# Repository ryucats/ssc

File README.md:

# Simple Serial Card

## Overview

The Simple Serial Card is a low-cost Super Serial Card work-a-like. I designed
this because I needed a way to use ADTPro on my Apple IIe, and the price of
super serial cards on eBay is getting a bit high for my taste.

This card is more or less 100% compatible with the original Apple card. It
uses the same 6551 ACIA mapped to the same I/O locations, and in fact can
use the same firmware ROM.  It does however have some minor differences in the
interest of cost:

1. There are no DIP switches, so you cannot set the default configuration. It
   does, however, include a jumper that can be removed to disable IRQs.
2. Instead of a DB-25 it is wired to use a DB-9 cable like those used by PC
   motherboards.
3. There is no terminal/modem block to change the serial port wiring. Just use
   the appropriate cable instead, or a null modem adapter.

The KiCAD schematics and PCB layout are included. It is a four layer board,
because my fab house of choice charges the same for 2 and 4 layers, so I went
with what made the layout easier.

## Parts List

* A 74LS245 octal bus transceiver (non-TTL appears to have issues with the ROM address decode logic) (U1)
* A 28-pin 27xx-series EPROM (JEDEC-compatible EEPROMs will also work) (U2)
* A 1.8432 MHz 5V oscillator (U3)
* A 22V10 GAL (any speed or variety should work) (U4)
* A W65C51N ACIA (U5)
* Two MAX232 RS-232 line transceivers (U6, U7)
* Seven 0.1uf ceramic bypass caps (C1-C7)
* Eight 1uf 16V electrolytic caps (C9-C16)
* A 2x5 pin header (J1)
* A 1x2 pin header (J2)

## Assembly

Before assembly you will need to burn firmware ROM into the EEPROM, and burn
the appropriat equations into the GAL. See "Burning the ROM" and "Burning the
GAL" below for more details.

I would suggest socketing all of the chips, but at the very least socket the
ROM and the GAL in case you need to update them.

As mentioned above the header on this card is wired the same as a PC COM
header. There are two varieties of these cables available; this card uses the
newer style which is wired 1:1; that is, pin 1 on the header goes to pin 1
on the DB-9, pin 2 to pin 2, etc. These are sometimes referred to as
"AT/EVEREX" style cables.

There is an asterisk on the card's silkscreen indicating pin one on the RS-232
header; make sure this lines up with pin one on your ribbon cable. Usually this
is the red wire on the ribbon cable.

## Installation

Turn off the computer, put the card in an empty slot, and mount the DB-9 on one
of the small cutouts on the back of the computer (or just run the ribbon cable
through an open cutout if you don't care).

## Design Considerations

Many parts choices were influenced by what I have already in my parts bin, even
if that makes the design non-optimal. For example, I used MAX3232 line drivers
because I have a ton of them. With 12V available on the slots I could've used
different parts and avoided all the charge pump caps, but I didn't feel like
buying more chips.

With the exception of the 22V10 GAL used for glue logic all parts in this design
are still actively available. The GALs are out of production but still readily
available on eBay or Aliexpress (though YMMV as far as quality).

## Burning the ROM

A standard super serial card image should work fine with this card, though
since there are no configuration switches the default settings after power on
or reset will be somewhat random.  Once I have working cards built I will be
creating a customized firmware ROM that sets the defaults to 9600 bps for the
ADT Pro bootstrap.

Since 2K EPROMs are nearly impossible to find I subbed in an AT28C256 EEPROM
(again, I had one already). Only the lower 2K is used by the card, so when
burning you can either duplicate the image 16 times, or fill the upper 30K
with zeroes or some other random data. In theory a AT28C64 EEPROM should also
work (and only waste 6K), but I don't have one to test, and a brief search
suggests they aren't any cheaper than the AT28C256 (presumably because they
are out of production).

I use the TL866 II+ USB programmer along with the minipro Linux client for my
ROM burns.

## Burning the GAL

The equations for the GAL are included as a .pld file for the GALasm program.
If you run Linux or another OS that can run GNU make then you should be able
to just type "make" in the "gal" subfolder to compile the equations into a
.jed file.  Burning this file requires a suitable programmer; I personally
use the same TL866 II+ that I use for burning ROMs, though at least at the time
of this writing the minipro client doesn't know how to burn GALs properly, so
you'll need to use the official client software, either on a Windows PC or
under Wine.

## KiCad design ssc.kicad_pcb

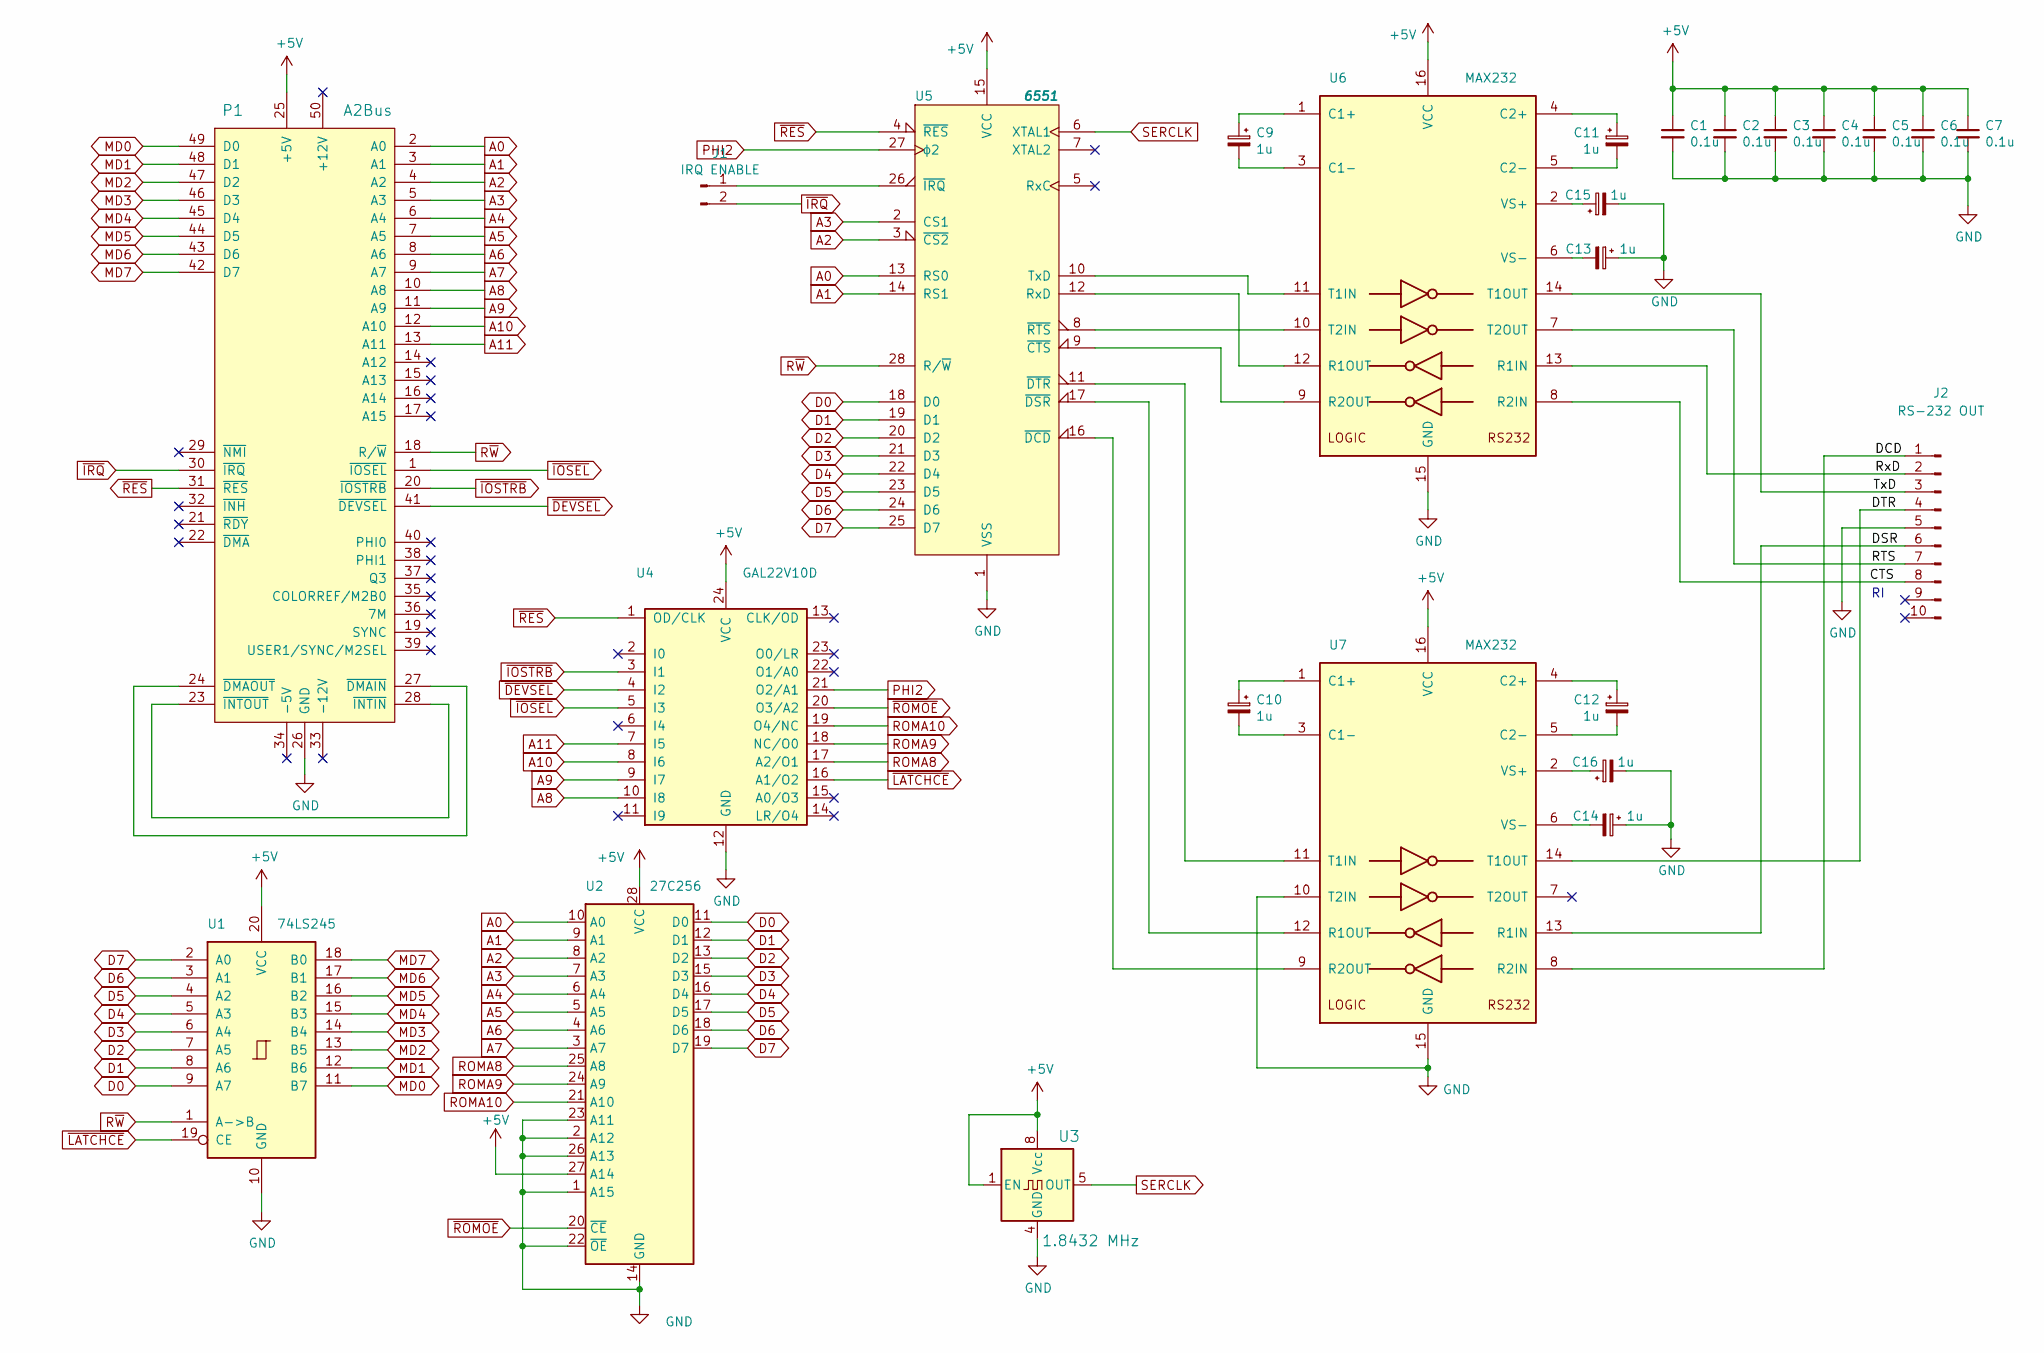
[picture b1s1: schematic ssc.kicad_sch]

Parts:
C1, C2, C3, C4, C5, C6, C7: 0.1u; C_Disc_D4.3mm_W1.9mm_P5.00mm
C9, C10, C11, C12, C13, C14, C15, C16: 1u; CP_Radial_D5.0mm_P2.50mm
J1: IRQ ENABLE; PinHeader_1x02_P2.54mm_Vertical
J2: RS-232 OUT; PinHeader_2x05_P2.54mm_Vertical
P1: A2Bus; Male_Card-Edge_50_pin__100_mil
U1: 74LS245; DIP-20_W7.62mm_Socket
U2: 27C256; DIP-28_W15.24mm
U3: 1.8432 MHz; Oscillator_DIP-8
U4: GAL22V10D; DIP-24_W7.62mm
U5: 6551; DIP-28_W15.24mm
U6, U7: MAX232; DIP-16_W7.62mm_Socket

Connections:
+5V: C1.1, C2.1, C3.1, C4.1, C5.1, C6.1, C7.1, P1.25 (+5V), U1.20 (VCC), U2.27 (A14), U2.28 (VCC), U4.24 (VCC), U5.15 (VCC), U6.16 (VCC), U7.16 (VCC); also elsewhere on the board
/CTS: J2.8, U6.8 (R2IN)
/DCD: J2.1, U7.8 (R2IN)
/DSR: J2.6, U7.13 (R1IN)
/DTR: J2.4, U7.14 (T1OUT)
/RTS: J2.7, U6.7 (T2OUT)
/RxD: J2.2, U6.13 (R1IN)
/TxD: J2.3, U6.14 (T1OUT)
A0: P1.2 (A0), U2.10 (A0), U5.13 (RS0)
A1: P1.3 (A1), U2.9 (A1), U5.14 (RS1)
A2: P1.4 (A2), U2.8 (A2), U5.3 (~CS2)
A3: P1.5 (A3), U2.7 (A3), U5.2 (CS1)
A4: P1.6 (A4), U2.6 (A4)
A5: P1.7 (A5), U2.5 (A5)
A6: P1.8 (A6), U2.4 (A6)
A7: P1.9 (A7), U2.3 (A7)
A8: P1.10 (A8), U4.10 (I8)
A9: P1.11 (A9), U4.9 (I7)
A10: P1.12 (A10), U4.8 (I6)
A11: P1.13 (A11), U4.7 (I5)
D0: U1.9 (A7), U2.11 (D0), U5.18 (D0)
D1: U1.8 (A6), U2.12 (D1), U5.19 (D1)
D2: U1.7 (A5), U2.13 (D2), U5.20 (D2)
D3: U1.6 (A4), U2.15 (D3), U5.21 (D3)
D4: U1.5 (A3), U2.16 (D4), U5.22 (D4)
D5: U1.4 (A2), U2.17 (D5), U5.23 (D5)
D6: U1.3 (A1), U2.18 (D6), U5.24 (D6)
D7: U1.2 (A0), U2.19 (D7), U5.25 (D7)
GND: C1.2, C2.2, C3.2, C4.2, C5.2, C6.2, C7.2, C13.1, C14.1, C15.2, C16.2, J2.5, P1.26 (GND), U1.10 (GND), U2.1 (A15), U2.2 (A12), U2.14 (GND), U2.22 (~OE), U2.23 (A11), U2.26 (A13), U4.12 (GND), U5.1 (VSS), U6.15 (GND), U7.10 (T2IN), U7.15 (GND); also elsewhere on the board
MD0: P1.49 (D0), U1.11 (B7)
MD1: P1.48 (D1), U1.12 (B6)
MD2: P1.47 (D2), U1.13 (B5)
MD3: P1.46 (D3), U1.14 (B4)
MD4: P1.45 (D4), U1.15 (B3)
MD5: P1.44 (D5), U1.16 (B2)
MD6: P1.43 (D6), U1.17 (B1)
MD7: P1.42 (D7), U1.18 (B0)
unnamed: J1.1, U5.26 (~IRQ)
unnamed: P1.24 (~DMAOUT), P1.27 (~DMAIN)
unnamed: P1.23 (~INTOUT), P1.28 (~INTIN)
unnamed: U5.12 (RxD), U6.12 (R1OUT)
unnamed: U5.10 (TxD), U6.11 (T1IN)
unnamed: U5.9 (~CTS), U6.9 (R2OUT)
unnamed: U5.16 (~DCD), U7.9 (R2OUT)
unnamed: U5.17 (~DSR), U7.12 (R1OUT)
unnamed: U5.11 (~DTR), U7.11 (T1IN)
unnamed: U5.8 (~RTS), U6.10 (T2IN)
unnamed: C9.1, U6.1 (C1+)
unnamed: C9.2, U6.3 (C1-)
unnamed: C11.1, U6.4 (C2+)
unnamed: C11.2, U6.5 (C2-)
unnamed: C15.1, U6.2 (VS+)
unnamed: C13.2, U6.6 (VS-)
unnamed: C10.1, U7.1 (C1+)
unnamed: C10.2, U7.3 (C1-)
unnamed: C12.1, U7.4 (C2+)
unnamed: C12.2, U7.5 (C2-)
unnamed: C16.1, U7.2 (VS+)
unnamed: C14.2, U7.6 (VS-)
PHI2: U4.21 (O2/A1), U5.27 (ϕ2)
ROMA8: U2.25 (A8), U4.17 (A2/O1)
ROMA9: U2.24 (A9), U4.18 (NC/O0)
ROMA10: U2.21 (A10), U4.19 (O4/NC)
R~W: P1.18 (R/~W), U1.1 (A->B), U5.28 (R/~W)
SERCLK: U5.6 (XTAL1); also elsewhere on the board
~DEVSEL: P1.41 (~DEVSEL), U4.4 (I2)
~IOSEL: P1.1 (~IOSEL), U4.5 (I3)
~IOSTRB: P1.20 (~IOSTRB), U4.3 (I1)
~IRQ: J1.2, P1.30 (~IRQ)
~LATCHCE: U1.19 (CE), U4.16 (A1/O2)
~RES: P1.31 (~RES), U4.1 (OD/CLK), U5.4 (~RES)
~ROMOE: U2.20 (~CE), U4.20 (O3/A2)

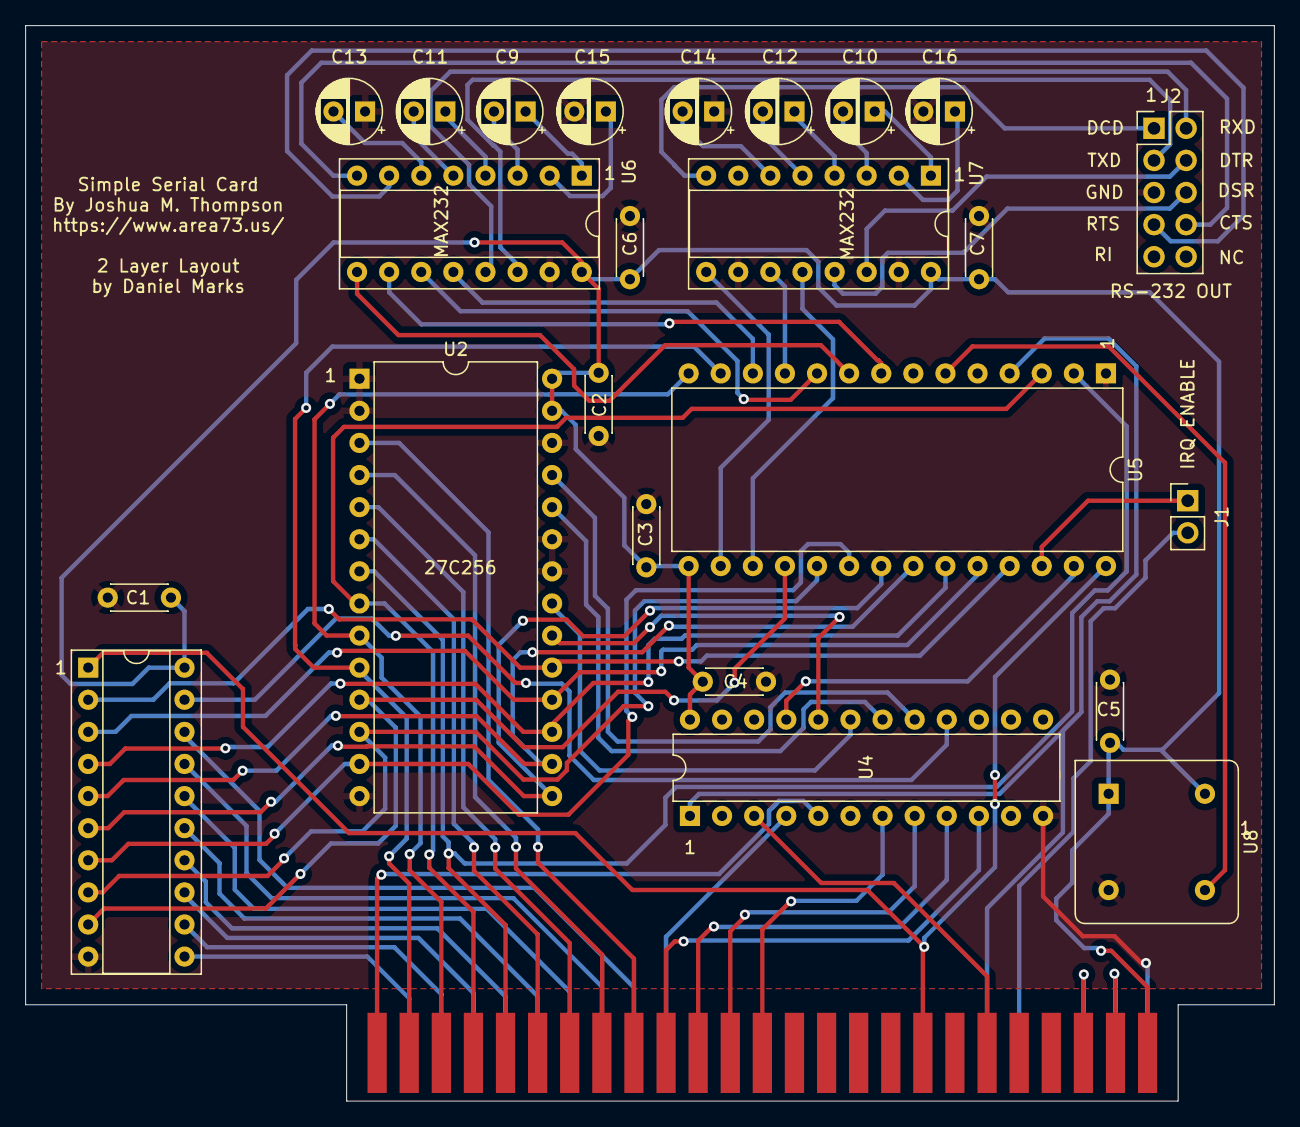
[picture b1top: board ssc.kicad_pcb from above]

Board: 2 copper layers, 98.8 x 85.1 mm, 25 parts (0 on the bottom side), 72 nets.

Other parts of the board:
U8: 1.8432 MHz; Oscillator_DIP-8

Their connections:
+5V: U8.1 (EN), U8.8 (Vcc); also elsewhere on the board
GND: U8.4 (GND); also elsewhere on the board
SERCLK: U8.5 (OUT); also elsewhere on the board

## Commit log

2023-03-13 Update ignored files.
2023-03-13 Checkpoint.
2023-03-14 Update .gitignore.
2023-03-14 Remove unused file.
2023-03-14 Update.
2023-03-14 Remove cache file.
